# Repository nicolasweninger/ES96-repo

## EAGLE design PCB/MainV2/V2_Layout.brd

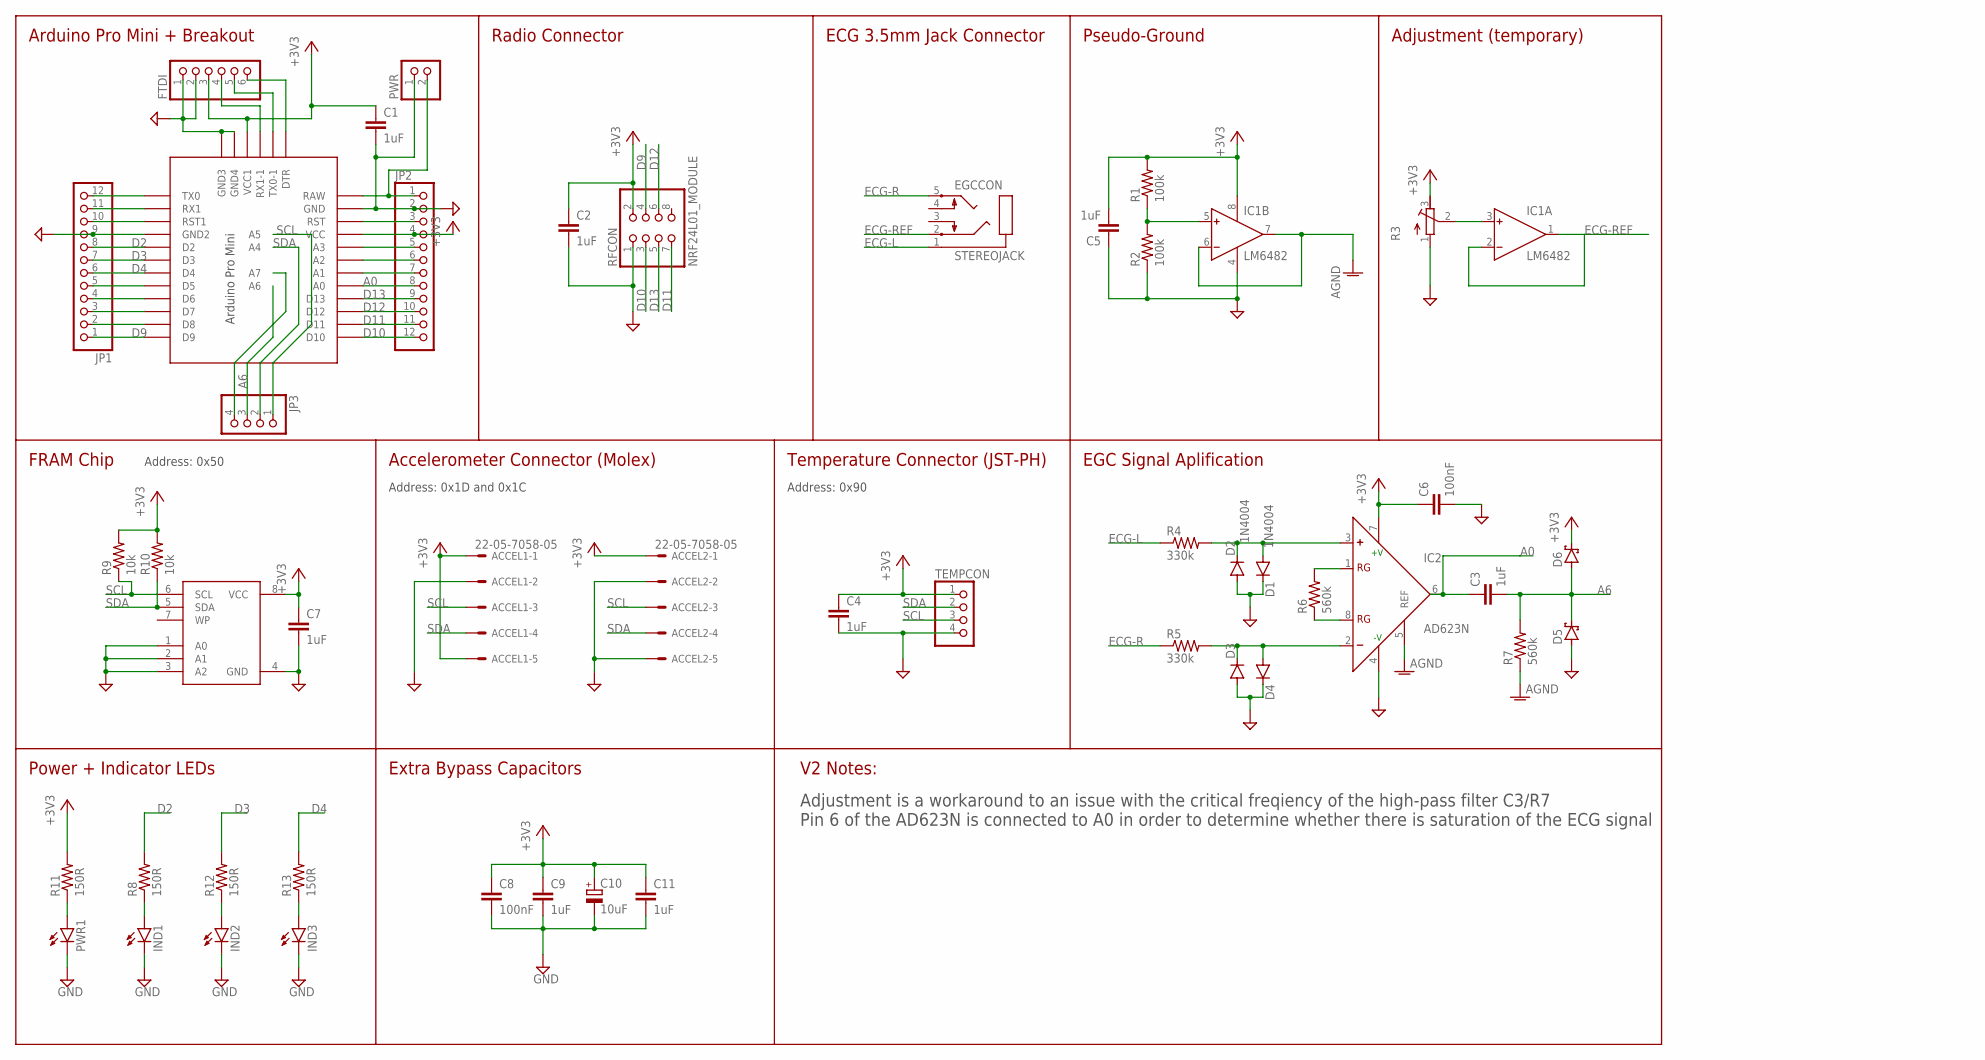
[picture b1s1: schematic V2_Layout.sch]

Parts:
ACCEL1, ACCEL2: 22-05-7058-05; 7395-05
C1, C2, C3, C4, C5, C7: 1uF; C0603
C6: 100nF; C0603
C8: 100nF; C025-030X050
C9, C11: 1uF; C025-030X050
C10: 10uF; TAP5-45
D1, D2, D3, D4: 1N4004; DO41-10
D5, D6: SCHOTTKY-DIODEDO35-7; DO35-7
EGCCON: STEREOJACK; STX3100
FTDI: PINHD-1X6; 1X06
IC1: LM6482; DIL08
IC2: AD623N; DIL08
IND1, IND2, IND3: LEDCHIPLED_0805; CHIPLED_0805
JP1, JP2: PINHD-1X12; 1X12
JP3: PINHD-1X4; 1X04
PWR: PINHD-1X2; 1X02
PWR1: LEDCHIPLED_0805; CHIPLED_0805
R1, R2: 100k; R0603
R3: R-TRIMM64P; RTRIM64P
R4, R5: 330k; R0603
R6, R7: 560k; R0603
R8, R11, R12, R13: 150R; R0603
R9, R10: 10k; R0603
RFCON: NRF24L01_MODULE; 2X04
TEMPCON: PINHD-1X4M; 1X04M
U2: MB85RC256VPF-G-JNERE2; SOIC8
U$1: PRO-MINI-2

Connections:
+3V3: ACCEL1.1, ACCEL1.5, ACCEL2.1, C1.1, C2.1, C4.1, C5.2, C6.1, C7.1, C8.1, C9.1, C10.+, C11.1, D6.C, FTDI.3, IC1.8 (V+), IC2.7 (+V), JP2.4, R1.2, R3.3 (E), R9.2, R10.2, R11.2, RFCON.2, TEMPCON.1, U2.8 (VCC), U$1.VCC, U$1.VCC1
A0: C3.1, IC2.6 (OUT), JP2.8, U$1.A3 (A0)
A6: C3.2, D5.C, D6.A, JP3.3, R7.2, U$1.A6
AGND: IC1.6 (IN-), IC1.7 (OUT), IC2.5 (REF), R7.1
D2: JP1.8, R8.2, U$1.D2
D3: JP1.7, R12.2, U$1.D3
D4: JP1.6, R13.2, U$1.D4
D5: JP1.5, U$1.D5
D6: JP1.4, U$1.D6
D7: JP1.3, U$1.D7
D8: JP1.2, U$1.D8
D9: JP1.1, RFCON.4, U$1.D9
D10: JP2.12, RFCON.3, U$1.D10
D11: JP2.11, RFCON.7, U$1.D11
D12: JP2.10, RFCON.6, U$1.D12
D13: JP2.9, RFCON.5, U$1.D13
ECG-L: EGCCON.1, R4.1
ECG-R: EGCCON.5, R5.1
ECG-REF: EGCCON.2, IC1.1 (OUT), IC1.2 (IN-)
GND: ACCEL1.2, ACCEL2.2, ACCEL2.5, C1.2, C2.2, C4.2, C5.1, C6.2, C7.2, C8.2, C9.2, C10.-, C11.2, D1.C, D2.A, D3.A, D4.C, D5.A, FTDI.1, FTDI.2, IC1.4 (V-), IC2.4 (-V), IND1.C, IND2.C, IND3.C, JP1.9, JP2.2, PWR.1, PWR1.C, R2.1, R3.1 (A), RFCON.1, TEMPCON.4, U2.1 (A0), U2.2 (A1), U2.3 (A2), U2.4 (GND), U$1.GND, U$1.GND1 (GND2), U$1.GND2 (GND3), U$1.GND3 (GND4)
unnamed: PWR1.A, R11.1
unnamed: D3.C, D4.A, IC2.2 (-), R5.2
unnamed: IC1.5 (IN+), R1.1, R2.2
unnamed: FTDI.4, U$1.RX1-1
unnamed: D1.A, D2.C, IC2.3 (+), R4.2
unnamed: IC2.8 (RG), R6.1
unnamed: IC2.1 (RG), R6.2
unnamed: JP1.12, U$1.TX0
unnamed: JP1.11, U$1.RX1
unnamed: JP1.10, U$1.RST1
unnamed: FTDI.5, U$1.TX0-1
unnamed: FTDI.6, U$1.DTR
unnamed: IND1.A, R8.1
unnamed: IND2.A, R12.1
unnamed: IND3.A, R13.1
unnamed: IC1.3 (IN+), R3.2 (S)
unnamed: JP2.1, PWR.2, U$1.RAW
unnamed: JP2.3, U$1.RST
unnamed: JP2.5, U$1.A0 (A3)
unnamed: JP2.6, U$1.A1 (A2)
unnamed: JP2.7, U$1.A2 (A1)
unnamed: JP3.4, U$1.A7
SCL: ACCEL1.3, ACCEL2.3, JP3.1, R9.1, TEMPCON.3, U2.6 (SCL), U$1.A5
SDA: ACCEL1.4, ACCEL2.4, JP3.2, R10.1, TEMPCON.2, U2.5 (SDA), U$1.A4

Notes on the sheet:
Arduino Pro Mini + Breakout
Radio Connector
FRAM Chip
Accelerometer Connector (Molex)
Temperature Connector (JST-PH)
ECG 3.5mm Jack Connector
Pseudo-Ground
EGC Signal Aplification
Address: 0x50
Power + Indicator LEDs
Extra Bypass Capacitors
Address: 0x1D and 0x1C
Address: 0x90
V2 Notes:
Adjustment (temporary)
Adjustment is a workaround to an issue with the critical freqiency of the high-pass filter C3/R7 Pin 6 of the AD623N is connected to A0 in order to determine whether there is saturation of the ECG signal

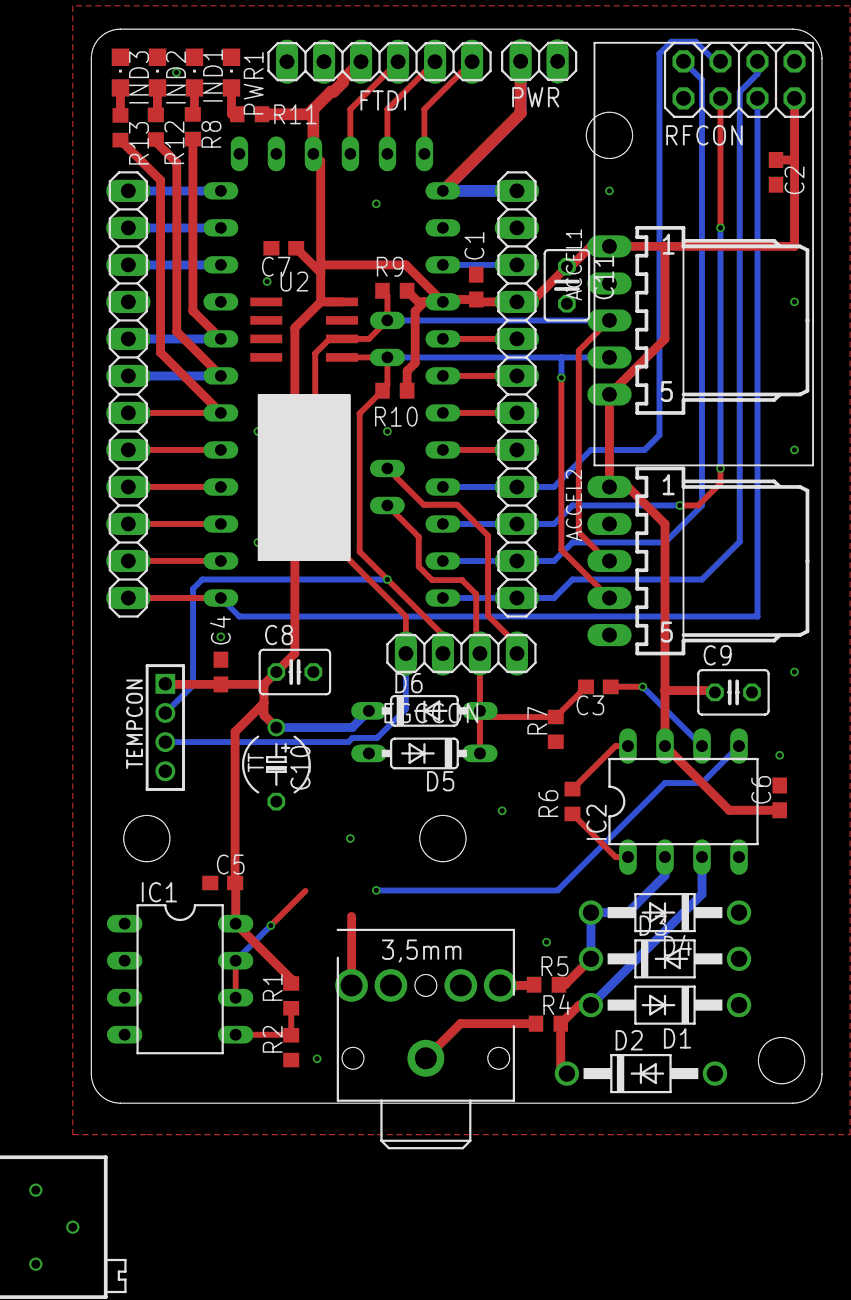
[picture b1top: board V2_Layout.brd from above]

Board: 2 copper layers, 50.1 x 73.7 mm, 48 parts (0 on the bottom side), 44 nets.

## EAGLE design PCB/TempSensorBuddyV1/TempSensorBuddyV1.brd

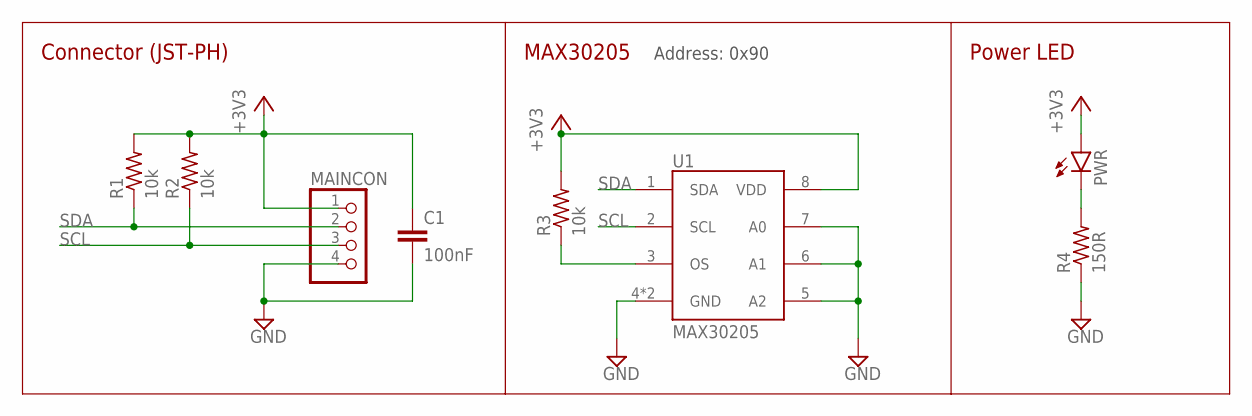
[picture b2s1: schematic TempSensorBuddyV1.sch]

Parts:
C1: 100nF; C0603
MAINCON: PINHD-1X4M; 1X04M
PWR: LEDCHIPLED_0805; CHIPLED_0805
R1, R2, R3: 10k; R0603
R4: 150R; R0603
U1: MAX30205; DFN-8

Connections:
+3V3: C1.1, MAINCON.1, PWR.A, R1.2, R2.2, R3.2, U1.8 (VDD)
GND: C1.2, MAINCON.4, R4.1, U1.4 (GND), U1.5 (A2), U1.6 (A1), U1.7 (A0), U1.9 (GND)
unnamed: R3.1, U1.3 (OS)
unnamed: PWR.C, R4.2
SCL: MAINCON.3, R2.1, U1.2 (SCL)
SDA: MAINCON.2, R1.1, U1.1 (SDA)

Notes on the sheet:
Address: 0x90
Connector (JST-PH)
MAX30205
Power LED

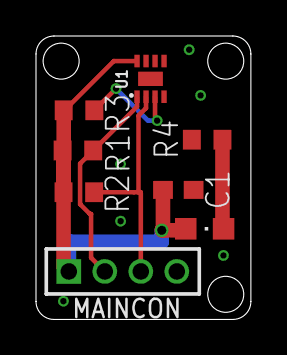
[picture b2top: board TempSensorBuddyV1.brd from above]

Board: 2 copper layers, 11.9 x 15.7 mm, 8 parts (0 on the bottom side), 6 nets.

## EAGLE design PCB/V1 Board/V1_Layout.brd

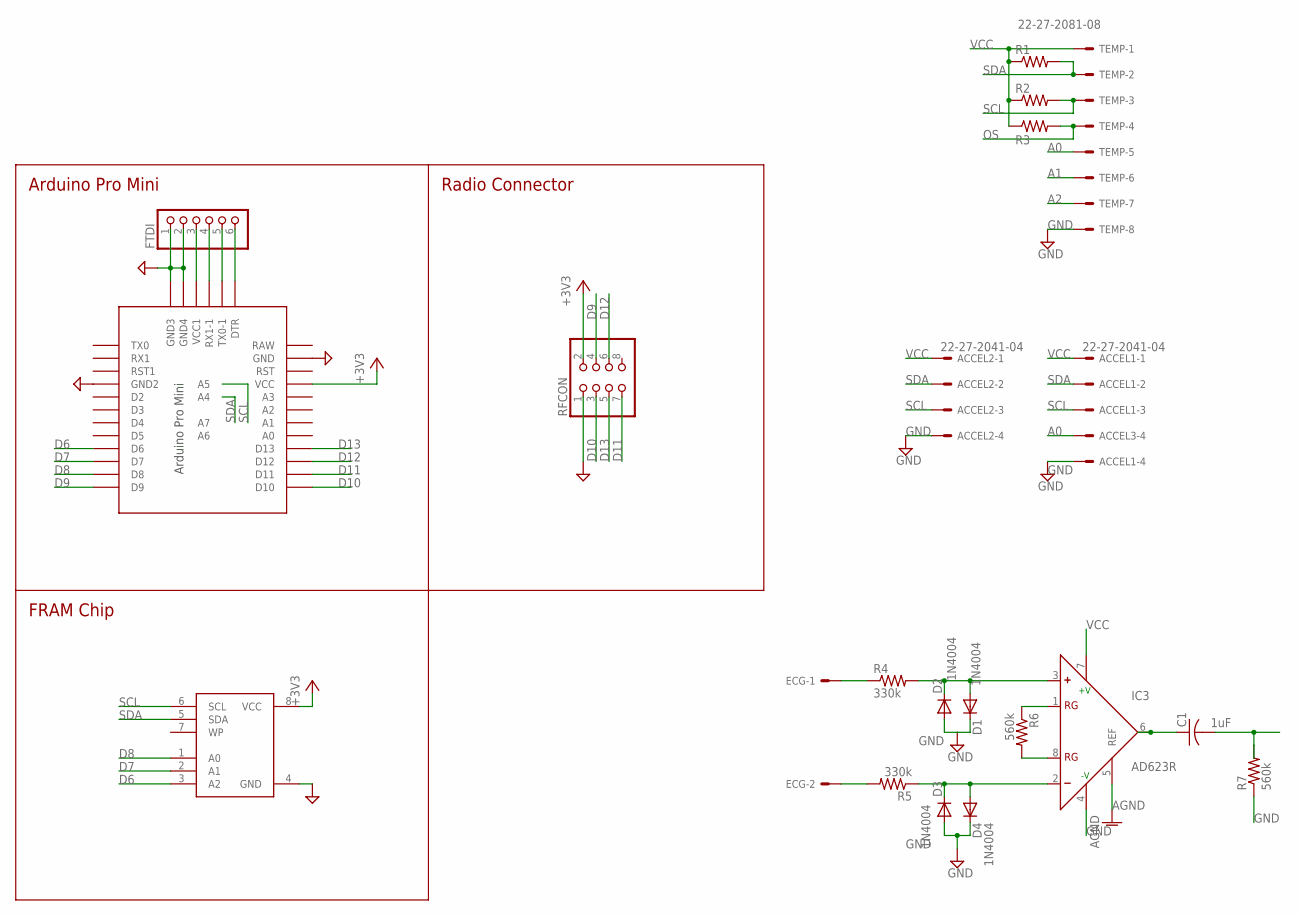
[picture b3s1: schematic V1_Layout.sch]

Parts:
ACCEL1, ACCEL2, ACCEL3: 22-27-2041-04; 6410-04
C1: 1uF; C0805
D1, D2, D3, D4: 1N4004; DO41-10
ECG: 22-27-2021-02; 6410-02
FTDI: PINHD-1X6; 1X06
IC3: AD623R; SO8
R1, R2, R3: R-US_R0805; R0805
R4, R5: 330k; R0805
R6, R7: 560k; R0805
RFCON: PINHD-2X4; 2X04
TEMP: 22-27-2081-08; 6410-08
U2: MB85RC256VPF-G-JNERE2; SOIC8
U$1: PRO-MINI-2

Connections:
+3V3: RFCON.2, U2.8 (VCC), U$1.VCC
A0: ACCEL3.4, TEMP.5
A1: TEMP.6
A2: TEMP.7
AGND: IC3.5 (REF)
D6: U2.3 (A2), U$1.D6
D7: U2.2 (A1), U$1.D7
D8: U2.1 (A0), U$1.D8
D9: RFCON.4, U$1.D9
D10: RFCON.3, U$1.D10
D11: RFCON.7, U$1.D11
D12: RFCON.6, U$1.D12
D13: RFCON.5, U$1.D13
GND: ACCEL1.4, ACCEL2.4, C1.2, D1.C, D2.A, D3.A, D4.C, FTDI.1, FTDI.2, IC3.4 (-V), R7.1, R7.2, RFCON.1, TEMP.8, U2.4 (GND), U$1.GND, U$1.GND1 (GND2), U$1.GND2 (GND3), U$1.GND3 (GND4)
unnamed: ECG.1, R4.1
unnamed: D3.C, D4.A, IC3.2 (-), R5.1
unnamed: ECG.2, R5.2
unnamed: D1.A, D2.C, IC3.3 (+), R4.2
unnamed: C1.1, IC3.6 (OUT)
unnamed: IC3.8 (RG), R6.2
unnamed: IC3.1 (RG), R6.1
unnamed: FTDI.6, U$1.DTR
unnamed: FTDI.5, U$1.TX0-1
unnamed: FTDI.4, U$1.RX1-1
unnamed: FTDI.3, U$1.VCC1
OS: R3.2, TEMP.4
SCL: ACCEL1.3, ACCEL2.3, R2.2, TEMP.3, U2.6 (SCL), U$1.A5
SDA: ACCEL1.2, ACCEL2.2, R1.2, TEMP.2, U2.5 (SDA), U$1.A4
VCC: ACCEL1.1, ACCEL2.1, IC3.7 (+V), R1.1, R2.1, R3.1, TEMP.1

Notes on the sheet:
Arduino Pro Mini
Radio Connector
FRAM Chip

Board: 2 copper layers, 22 parts (0 on the bottom side), 26 nets, no tracks yet.

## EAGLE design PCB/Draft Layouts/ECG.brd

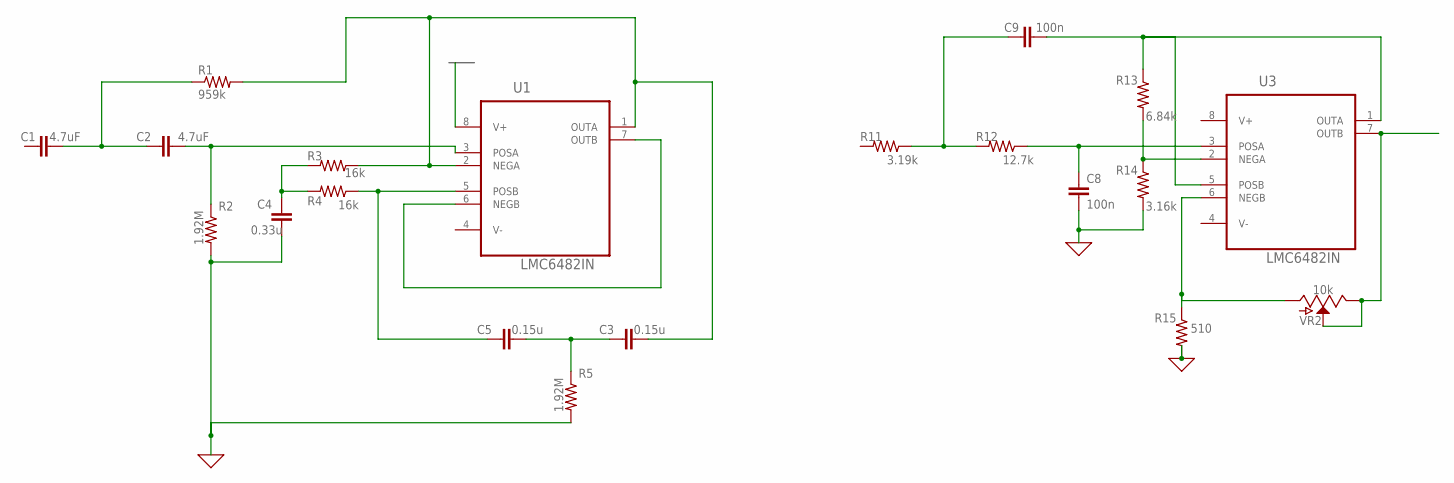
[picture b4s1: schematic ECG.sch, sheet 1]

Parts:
C1, C2: 4.7uF; 0603
C3, C5: 0.15u; C075-042X103
C4: 0.33u; C075-042X103
C8, C9: 100n; C025-025X050
R1: 959k; R0805
R2, R5: 1.92M; R0805
R3, R4: 16k; R0805
R11: 3.19k; R0805
R12: 12.7k; R0805
R13: 6.84k; R0805
R14: 3.16k; R0805
R15: 510; R0805
U1, U3: LMC6482IN; DIP254P762X508-8
VR2: 10k; SLIDER-SMALL

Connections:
0: C4.2, C8.2, R2.2, R5.2, R14.2, R15.2
B$3: U1.8 (V+)
unnamed: C1.2, C2.1, R1.1
unnamed: C2.2, R2.1, U1.3 (POSA)
unnamed: C3.2, R1.2, R3.1, U1.1 (OUTA), U1.2 (NEGA)
unnamed: C4.1, R3.2, R4.2
unnamed: C5.1, R4.1, U1.5 (POSB)
unnamed: U1.6 (NEGB), U1.7 (OUTB)
unnamed: C3.1, C5.2, R5.1
unnamed: C8.1, R12.1, U3.3 (POSA)
unnamed: C9.1, R11.1, R12.2
unnamed: C9.2, R13.1, U3.1 (OUTA), U3.5 (POSB)
unnamed: R13.2, R14.1, U3.2 (NEGA)
unnamed: R15.1, U3.6 (NEGB), VR2.BOTTOM (A)
unnamed: U3.7 (OUTB), VR2.TOP (E), VR2.WIPER (S)
V+: U3.8 (V+)
V-: U1.4 (V-), U3.4 (V-)

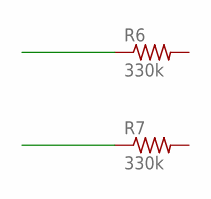
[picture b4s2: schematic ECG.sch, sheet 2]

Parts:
R6, R7: 330k; R0805

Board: 2 copper layers, 22 parts (0 on the bottom side), 15 nets, no tracks yet.

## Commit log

2018-11-07 First Arduino code commit
2018-11-08 deleted test
2018-11-15 init PCB dir
2018-11-15 deleted junk
2018-11-15 Aileen's AccelTemp Draft
2018-11-15 Arduino changed
2018-11-15 added gitignore
2018-11-15 ignore DS_Store files
2018-11-15 deteled junk
2018-11-15 blah
2018-11-15 added Awnit's ECG draft layouts
2018-11-18 adding pinheads
2018-11-19 removed cashe files
2018-11-19 Aileen's updates
2018-11-19 new custom parts library
2018-11-19 Initial commit of V1 working
2018-11-19 working on schematic, and first commit of temperature buddy board
2018-11-20 Changes ready for digital schematic design review (ECG STILL TODO)
2018-11-21 main schematic ready for review
2018-11-21 Schematic cleanup, added bypass caps, added inndicator LEDs
2018-11-21 Review changes complete. Starting layout
2018-11-21 Finished routing Temp Buddy Board. Please review.
2018-11-21 rounded corners on Temp Buddy board
2018-11-22 started initial main layout. Cleaned up files.
2018-11-22 First draft of completed layout and route
2018-11-22 Reviewed layout, added text, rounded corners. Design rule check passed. Ready for final review
2018-11-22 Ordered. Added CAM files. Added 3D desgn files for Fusion 360.
2018-11-26 Added comments in schematc
2018-12-17 Undid changes to V1 after manufacture and created MainV2 for desired meddling
2018-12-17 Included workarounds in V2 schematic
2018-12-28 final ES96 code push

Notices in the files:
parts and their libraries:
SparkFun-Capacitors: Licensing: Creative Commons ShareAlike 4.0 International - https://creativecommons.org/licenses/by-sa/4.0
